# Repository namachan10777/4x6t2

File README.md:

# 4x6t2

[Imgur](https://i.imgur.com/xArgN0v.jpg)

A splited keyboard.
# License
MIT License 
Copyright (c) 2018 Nakano Masaki
## Exception
 * ./pcb/lib/4x6t2.pretty/MX_ALPS_KH_u1.00.kicad_mod
 * ./pcb/lib/4x6t2.pretty/D_SOD-123.kicad_mod
 * ./pcb/lib/4x6t2.pretty/LED_D3.0mm.kicad_mod
 * ./pcb/lib/4x6t2.pretty/R_Axial.kicad_mod
 * ./pcb/lib/4x6t2.pretty/SW_Tactile_SPST_Angled.kicad_mod
These footprint's original author is KiCAD.
These are distributed under CC-BY-SA 4.0.

# Third party
## helix
### point of use
 * Key footprint (./pcb/lib/4x6t2.pretty/MX_ALPS_KH_u1.00.kicad_mod) (modified)
 * Audio Jack footprint (./pcb/lib/4x6t2.pretty/MJ-4PP-9_rev2.kicad_mod)
### LICENSE
>Copyright (c) 2018 MakotoKurauchi
>
>Permission is hereby granted, free of charge, to any person obtaining a copy
>of this software and associated documentation files (the "Software"), to deal
>in the Software without restriction, including without limitation the rights
>to use, copy, modify, merge, publish, distribute, sublicense, and/or sell
>copies of the Software, and to permit persons to whom the Software is
>furnished to do so, subject to the following conditions:
>
>The above copyright notice and this permission notice shall be included in all
>copies or substantial portions of the Software.
>
>THE SOFTWARE IS PROVIDED "AS IS", WITHOUT WARRANTY OF ANY KIND, EXPRESS OR
>IMPLIED, INCLUDING BUT NOT LIMITED TO THE WARRANTIES OF MERCHANTABILITY,
>FITNESS FOR A PARTICULAR PURPOSE AND NONINFRINGEMENT. IN NO EVENT SHALL THE
>AUTHORS OR COPYRIGHT HOLDERS BE LIABLE FOR ANY CLAIM, DAMAGES OR OTHER
>LIABILITY, WHETHER IN AN ACTION OF CONTRACT, TORT OR OTHERWISE, ARISING FROM,
>OUT OF OR IN CONNECTION WITH THE SOFTWARE OR THE USE OR OTHER DEALINGS IN THE
>SOFTWARE.

## KiCAD Library
### LICENSE
CC-BY-SA 4.0
Copyright (c) KiCAD

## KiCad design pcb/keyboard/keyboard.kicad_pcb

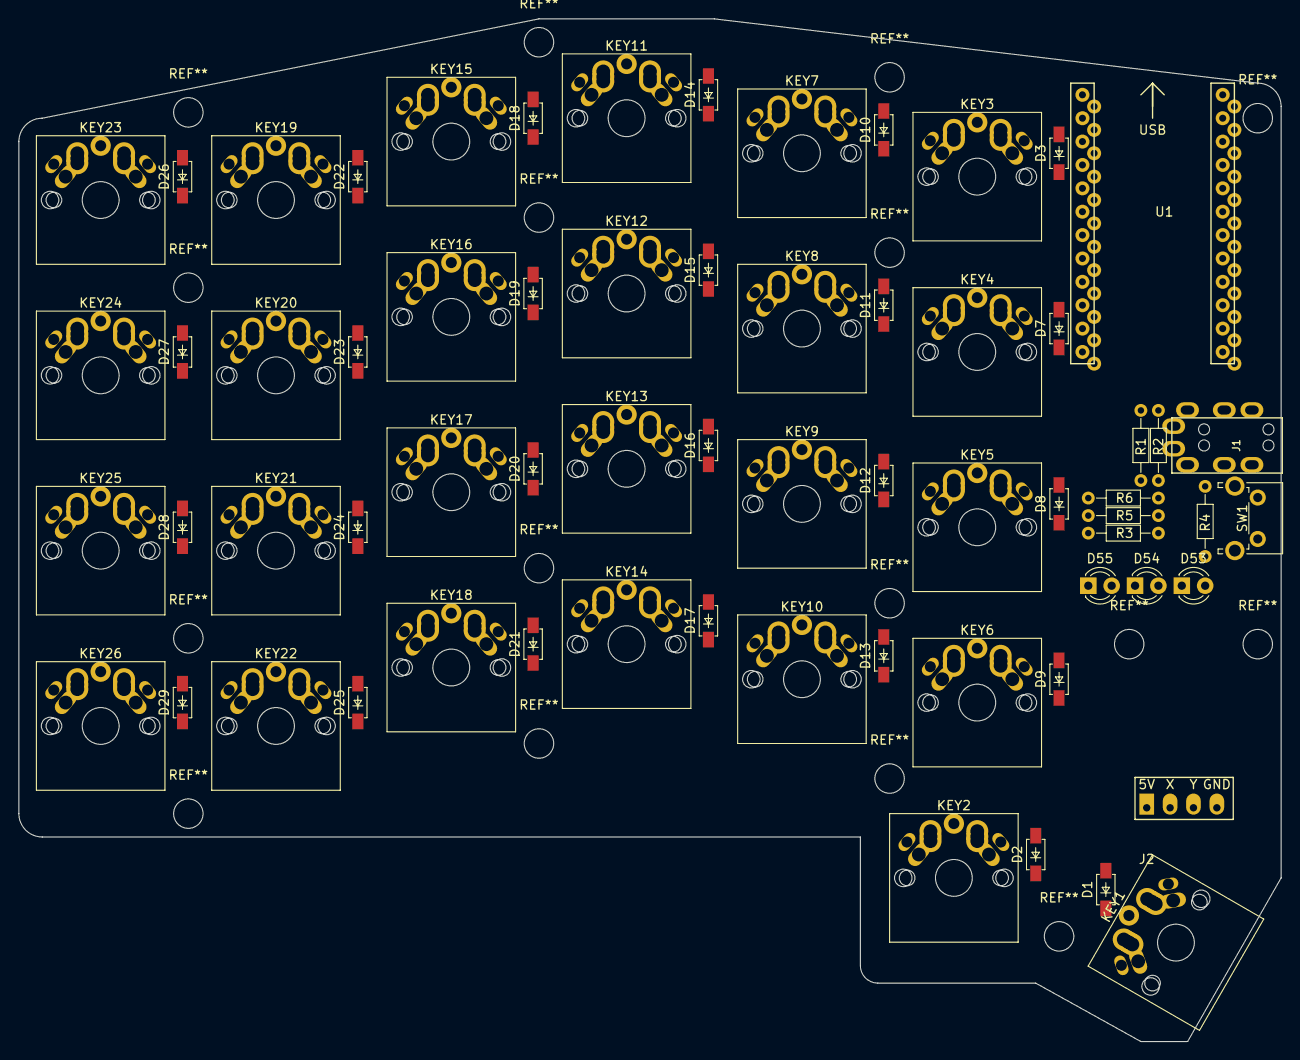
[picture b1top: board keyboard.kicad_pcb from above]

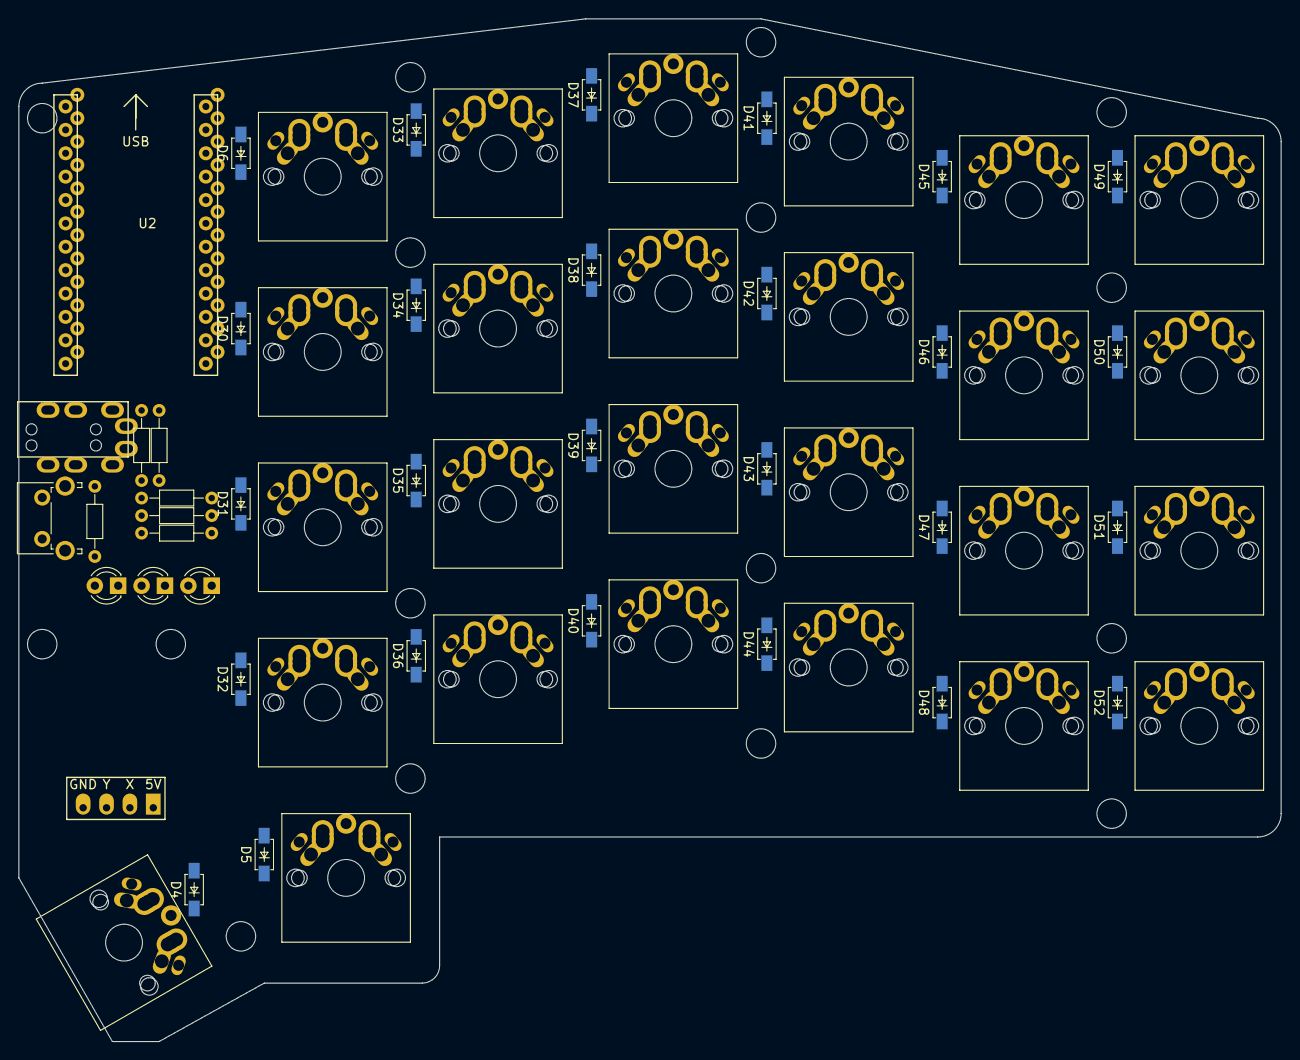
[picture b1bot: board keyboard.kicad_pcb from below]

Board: 2 copper layers, 137.2 x 111.1 mm, 92 parts (27 on the bottom side), 50 nets, no tracks yet.

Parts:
D1, D2, D3, D4, D5, D6, D7, D8, D9, D10, D11, D12, D13, D14, D15, D16, D17, D18, D19, D20, D21, D22, D23, D24, D25, D26, D27, D28, D29, D30, D31, D32, D33, D34, D35, D36, D37, D38, D39, D40, D41, D42, D43, D44, D45, D46, D47, D48, D49, D50, D51, D52: D; D_SOD-123
D53, D54, D55: LED; LED_D3.0mm
J1: Audio-Jack-4; MJ-4PP-9_rev2
J2: sidebutton; Wirepad_01x04
KEY1: KEY20; MX_ALPS_KH_u1.00
KEY2: KEY30; MX_ALPS_KH_u1.00
KEY3: KEY01; MX_ALPS_KH_u1.00
KEY4: KEY11; MX_ALPS_KH_u1.00
KEY5: KEY21; MX_ALPS_KH_u1.00
KEY6: KEY31; MX_ALPS_KH_u1.00
KEY7: KEY02; MX_ALPS_KH_u1.00
KEY8: KEY12; MX_ALPS_KH_u1.00
KEY9: KEY22; MX_ALPS_KH_u1.00
KEY10: KEY32; MX_ALPS_KH_u1.00
KEY11: KEY03; MX_ALPS_KH_u1.00
KEY12: KEY13; MX_ALPS_KH_u1.00
KEY13: KEY23; MX_ALPS_KH_u1.00
KEY14: KEY33; MX_ALPS_KH_u1.00
KEY15: KEY04; MX_ALPS_KH_u1.00
KEY16: KEY14; MX_ALPS_KH_u1.00
KEY17: KEY24; MX_ALPS_KH_u1.00
KEY18: KEY34; MX_ALPS_KH_u1.00
KEY19: KEY05; MX_ALPS_KH_u1.00
KEY20: KEY15; MX_ALPS_KH_u1.00
KEY21: KEY25; MX_ALPS_KH_u1.00
KEY22: KEY35; MX_ALPS_KH_u1.00
KEY23: KEY06; MX_ALPS_KH_u1.00
KEY24: KEY16; MX_ALPS_KH_u1.00
KEY25: KEY26; MX_ALPS_KH_u1.00
KEY26: KE36; MX_ALPS_KH_u1.00
R1, R2: 10kΩ; R_Axial
R3, R5, R6: 100Ω; R_Axial
R4: R; R_Axial
SW1: RESET_SW; SW_Tactile_SPST_Angled
U1, U2: Arduino_Pro_Micro

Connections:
+5V: J1.3, J2.1, R1.1, R2.1, R3.1, R4.1, R5.1, R6.1, U1.21, U2.21
/COL0: D1.2, D2.2, D4.2, D5.2, U1.17, U2.17
/COL1: D3.2, D6.2, D7.2, D8.2, D9.2, D30.2, D31.2, D32.2, U1.16, U2.16
/COL2: D10.2, D11.2, D12.2, D13.2, D33.2, D34.2, D35.2, D36.2, U1.15, U2.15
/COL3: D14.2, D15.2, D16.2, D17.2, D37.2, D38.2, D39.2, D40.2, U1.14, U2.14
/COL4: D18.2, D19.2, D20.2, D21.2, D41.2, D42.2, D43.2, D44.2, U1.13, U2.13
/COL5: D22.2, D23.2, D24.2, D25.2, D45.2, D46.2, D47.2, D48.2, U1.11, U2.11
/COL6: D26.2, D27.2, D28.2, D29.2, D49.2, D50.2, D51.2, D52.2, U1.12, U2.12
/LED1: D53.1, U1.20, U2.20
/LED2: D54.1, U1.19, U2.19
/LED3: D55.1, U1.18, U2.18
/ROW0: KEY3.1, KEY7.1, KEY11.1, KEY15.1, KEY19.1, KEY23.1, U1.1, U2.1
/ROW1: KEY4.1, KEY8.1, KEY12.1, KEY16.1, KEY20.1, KEY24.1, U1.2, U2.2
/ROW2: KEY1.1, KEY5.1, KEY9.1, KEY13.1, KEY17.1, KEY21.1, KEY25.1, U1.8, U2.8
/ROW4: KEY2.1, KEY6.1, KEY10.1, KEY14.1, KEY18.1, KEY22.1, KEY26.1, U1.10, U2.10
/RST: R4.2, SW1.1, U1.22, U2.22
/SCL: J1.1, R1.2, U1.6, U2.6
/SDA: J1.2, R2.2, U1.5, U2.5
/X: J2.2, U1.9, U2.9
/Y: J2.3, U1.7, U2.7
GND: J1.4, J2.4, SW1.2, U1.3, U1.4, U1.23, U2.3, U2.4, U2.23
unnamed: D1.1, D4.1, KEY1.2
unnamed: D2.1, D5.1, KEY2.2
unnamed: D3.1, D6.1, KEY3.2
unnamed: D10.1, D33.1, KEY7.2
unnamed: D11.1, D34.1, KEY8.2
unnamed: D12.1, D35.1, KEY9.2
unnamed: D13.1, D36.1, KEY10.2
unnamed: D14.1, D37.1, KEY11.2
unnamed: D15.1, D38.1, KEY12.2
unnamed: D16.1, D39.1, KEY13.2
unnamed: D17.1, D40.1, KEY14.2
unnamed: D18.1, D41.1, KEY15.2
unnamed: D19.1, D42.1, KEY16.2
unnamed: D20.1, D43.1, KEY17.2
unnamed: D21.1, D44.1, KEY18.2
unnamed: D22.1, D45.1, KEY19.2
unnamed: D23.1, D46.1, KEY20.2
unnamed: D24.1, D47.1, KEY21.2
unnamed: D25.1, D48.1, KEY22.2
unnamed: D26.1, D49.1, KEY23.2
unnamed: D27.1, D50.1, KEY24.2
unnamed: D28.1, D51.1, KEY25.2
unnamed: D29.1, D52.1, KEY26.2
unnamed: D7.1, D30.1, KEY4.2
unnamed: D8.1, D31.1, KEY5.2
unnamed: D9.1, D32.1, KEY6.2
unnamed: D53.2, R3.2
unnamed: D54.2, R5.2
unnamed: D55.2, R6.2

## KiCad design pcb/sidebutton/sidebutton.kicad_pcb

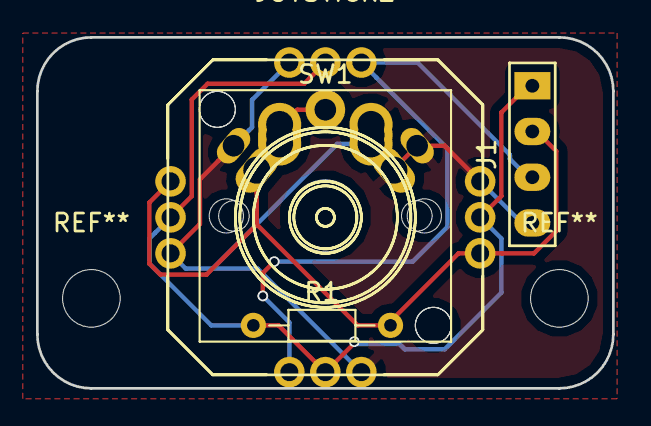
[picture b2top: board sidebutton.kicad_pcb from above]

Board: 2 copper layers, 32.0 x 19.5 mm, 5 parts (0 on the bottom side), 4 nets.

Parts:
J1: Conn_01x04; Wirepad_01x04
JOYSTICK1, JOYSTICK2: JT8P-3.2T-B10K-1-16Y
R1: R; R_Axial_DIN0204_L3.6mm_D1.6mm_P7.62mm_Horizontal
SW1: SW_DIP_x01; MX_ALPS_KH_u1.00

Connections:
+5V: J1.1, JOYSTICK1.2, JOYSTICK1.5, JOYSTICK2.2, JOYSTICK2.5, R1.1
/out1: J1.2, JOYSTICK1.4, JOYSTICK2.4, R1.2, SW1.2
/out2: J1.3, JOYSTICK1.1, JOYSTICK2.1
GND: J1.4, JOYSTICK1.3, JOYSTICK1.6, JOYSTICK2.3, JOYSTICK2.6, SW1.1

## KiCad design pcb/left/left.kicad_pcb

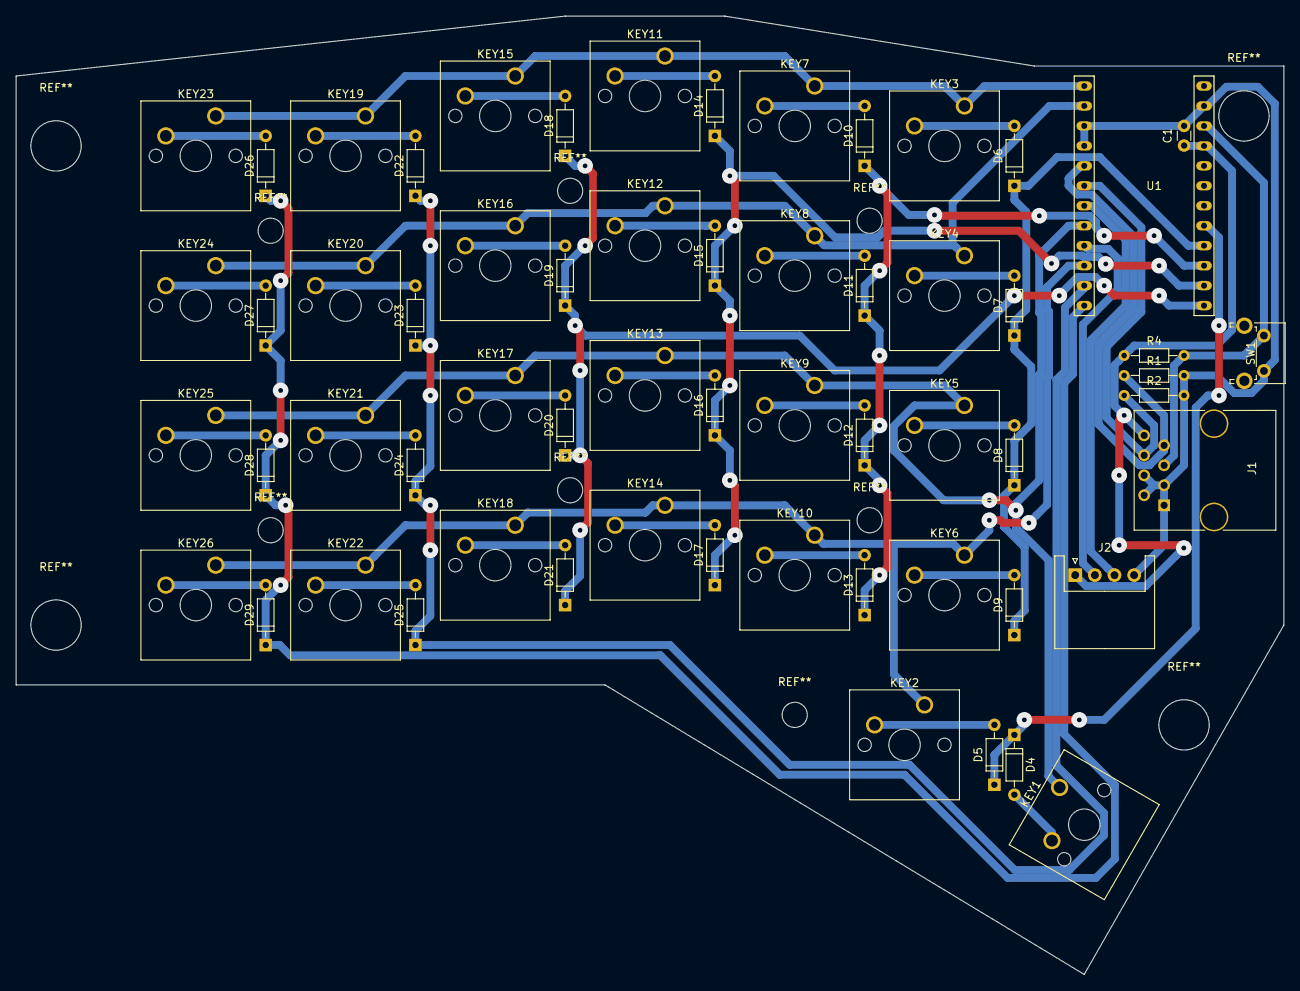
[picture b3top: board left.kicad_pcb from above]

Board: 2 copper layers, 161.3 x 121.9 mm, 60 parts (0 on the bottom side), 44 nets.

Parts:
C1: C; C_Disc_D3.0mm_W1.6mm_P2.50mm
D4, D5, D6, D7, D8, D9, D10, D11, D12, D13, D14, D15, D16, D17, D18, D19, D20, D21, D22, D23, D24, D25, D26, D27, D28, D29: D; D_DO-35_SOD27_P7.62mm_Horizontal
J1: RJ45-8pin; RJ45_8
J2: sidebutton; JST_XH_S04B-XH-A_04x2.50mm_Angled
KEY1: KEY20; SW_Cherry_MX1A_1.00u_PCB
KEY2: KEY30; SW_Cherry_MX1A_1.00u_PCB
KEY3: KEY01; SW_Cherry_MX1A_1.00u_PCB
KEY4: KEY11; SW_Cherry_MX1A_1.00u_PCB
KEY5: KEY21; SW_Cherry_MX1A_1.00u_PCB
KEY6: KEY31; SW_Cherry_MX1A_1.00u_PCB
KEY7: KEY02; SW_Cherry_MX1A_1.00u_PCB
KEY8: KEY12; SW_Cherry_MX1A_1.00u_PCB
KEY9: KEY22; SW_Cherry_MX1A_1.00u_PCB
KEY10: KEY32; SW_Cherry_MX1A_1.00u_PCB
KEY11: KEY03; SW_Cherry_MX1A_1.00u_PCB
KEY12: KEY13; SW_Cherry_MX1A_1.00u_PCB
KEY13: KEY23; SW_Cherry_MX1A_1.00u_PCB
KEY14: KEY33; SW_Cherry_MX1A_1.00u_PCB
KEY15: KEY04; SW_Cherry_MX1A_1.00u_PCB
KEY16: KEY14; SW_Cherry_MX1A_1.00u_PCB
KEY17: KEY24; SW_Cherry_MX1A_1.00u_PCB
KEY18: KEY34; SW_Cherry_MX1A_1.00u_PCB
KEY19: KEY05; SW_Cherry_MX1A_1.00u_PCB
KEY20: KEY15; SW_Cherry_MX1A_1.00u_PCB
KEY21: KEY25; SW_Cherry_MX1A_1.00u_PCB
KEY22: KEY35; SW_Cherry_MX1A_1.00u_PCB
KEY23: KEY06; SW_Cherry_MX1A_1.00u_PCB
KEY24: KEY16; SW_Cherry_MX1A_1.00u_PCB
KEY25: KEY26; SW_Cherry_MX1A_1.00u_PCB
KEY26: KE36; SW_Cherry_MX1A_1.00u_PCB
R1, R2: 10kΩ; R_Axial_DIN0204_L3.6mm_D1.6mm_P7.62mm_Horizontal
R4: R; R_Axial_DIN0204_L3.6mm_D1.6mm_P7.62mm_Horizontal
SW1: RESET_SW; SW_Tactile_SPST_Angled_PTS645Vx31-2LFS
U1: Arduino_Pro_Micro

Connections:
+5V: C1.1, J1.8, J2.1, R4.1, U1.21
/COL0: D4.1, D5.1, U1.17
/COL1: D6.1, D7.1, D8.1, D9.1, U1.16
/COL2: D10.1, D11.1, D12.1, D13.1, U1.15
/COL3: D14.1, D15.1, D16.1, D17.1, U1.14
/COL4: D18.1, D19.1, D20.1, D21.1, U1.13
/COL5: D22.1, D23.1, D24.1, D25.1, U1.11
/COL6: D26.1, D27.1, D28.1, D29.1, U1.12
/ROW0: KEY3.1, KEY7.1, KEY11.1, KEY15.1, KEY19.1, KEY23.1, U1.1
/ROW1: KEY4.1, KEY8.1, KEY12.1, KEY16.1, KEY20.1, KEY24.1, U1.2
/ROW2: KEY1.1, KEY5.1, KEY9.1, KEY13.1, KEY17.1, KEY21.1, KEY25.1, U1.8
/ROW4: KEY2.1, KEY6.1, KEY10.1, KEY14.1, KEY18.1, KEY22.1, KEY26.1, U1.10
/RST: J1.5, R4.2, SW1.1, U1.22
/SCL: J1.6, R2.1, U1.6
/SDA: J1.7, R1.1, U1.5
/X: J2.2, U1.9
/Y: J2.3, U1.7
GND: C1.2, J1.1, J1.2, J1.3, J1.4, J2.4, R1.2, R2.2, SW1.2, U1.3, U1.4, U1.23
unnamed: D4.2, KEY1.2
unnamed: D5.2, KEY2.2
unnamed: D6.2, KEY3.2
unnamed: D7.2, KEY4.2
unnamed: D8.2, KEY5.2
unnamed: D9.2, KEY6.2
unnamed: D10.2, KEY7.2
unnamed: D11.2, KEY8.2
unnamed: D12.2, KEY9.2
unnamed: D13.2, KEY10.2
unnamed: D14.2, KEY11.2
unnamed: D15.2, KEY12.2
unnamed: D16.2, KEY13.2
unnamed: D17.2, KEY14.2
unnamed: D18.2, KEY15.2
unnamed: D19.2, KEY16.2
unnamed: D20.2, KEY17.2
unnamed: D21.2, KEY18.2
unnamed: D22.2, KEY19.2
unnamed: D23.2, KEY20.2
unnamed: D24.2, KEY21.2
unnamed: D25.2, KEY22.2
unnamed: D26.2, KEY23.2
unnamed: D27.2, KEY24.2
unnamed: D28.2, KEY25.2
unnamed: D29.2, KEY26.2

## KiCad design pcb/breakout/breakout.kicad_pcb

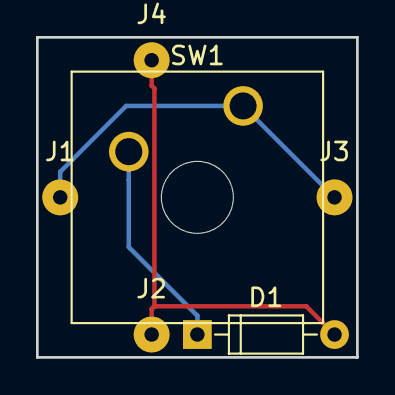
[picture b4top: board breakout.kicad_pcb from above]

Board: 2 copper layers, 17.8 x 17.8 mm, 6 parts (0 on the bottom side), 3 nets.

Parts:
D1: D; D_DO-35_SOD27_P7.62mm_Horizontal
J1, J2, J3, J4: Conn_01x01; SolderWirePad_single_0-8mmDrill
SW1: SW_DIP_x01; SW_Cherry_MX1A_1.00u_Plate

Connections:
unnamed: D1.1, SW1.2
unnamed: D1.2, J2.1, J4.1
unnamed: J1.1, J3.1, SW1.1

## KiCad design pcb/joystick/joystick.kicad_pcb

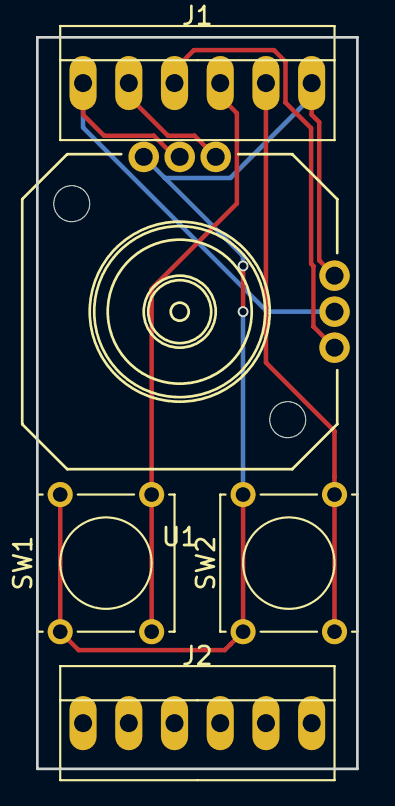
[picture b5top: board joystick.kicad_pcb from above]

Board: 2 copper layers, 17.8 x 40.6 mm, 5 parts (0 on the bottom side), 6 nets.

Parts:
J1, J2: Conn_01x06; PINHEAD1-6
SW1, SW2: SW_DIP_x01; SW_Tactile_Straight_KSL0Axx1LFTR
U1: JT8P-3.2T-B10K-1-16Y

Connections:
+5V: J1.1, U1.2, U1.5
/sw1: J1.4, SW1.2
/sw2: J1.5, SW2.2
/x: J1.3, U1.4
/y: J1.2, U1.1
GND: J1.6, SW1.1, SW2.1, U1.3, U1.6

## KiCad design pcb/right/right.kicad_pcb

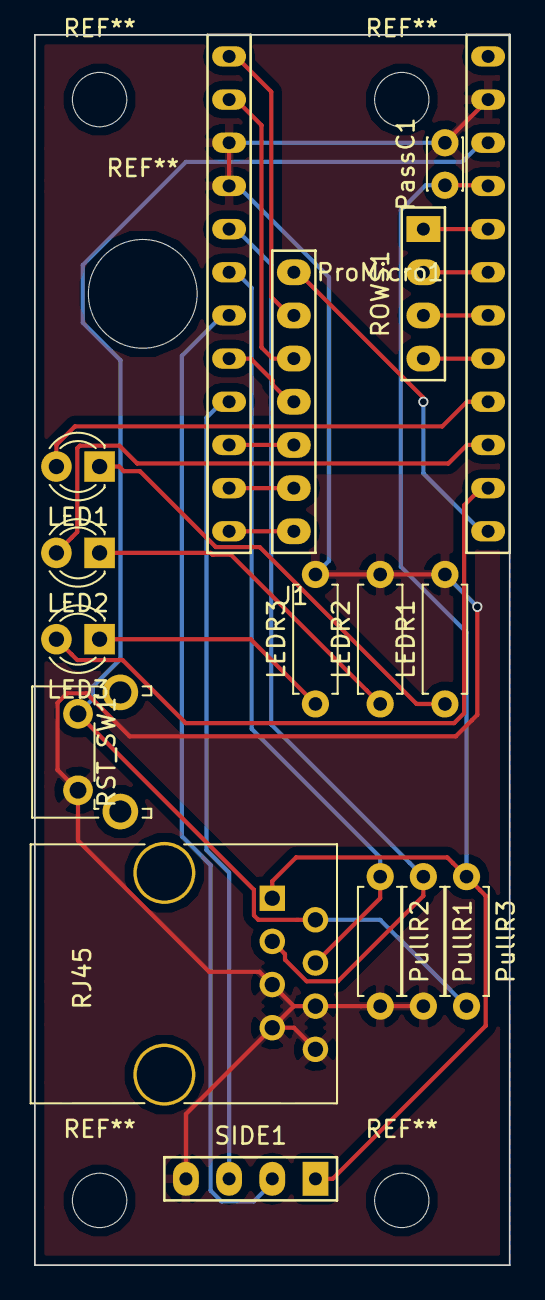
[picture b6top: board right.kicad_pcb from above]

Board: 2 copper layers, 27.9 x 72.4 mm, 16 parts (0 on the bottom side), 24 nets.

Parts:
J1: Conn_01x07; Wirepad_01x07
LED1: LED1; LED_D3.0mm
LED2: LED2; LED_D3.0mm
LED3: LED3; LED_D3.0mm
LEDR1: LED1_R; R_Axial_DIN0207_L6.3mm_D2.5mm_P7.62mm_Horizontal
LEDR2: LED2_R; R_Axial_DIN0207_L6.3mm_D2.5mm_P7.62mm_Horizontal
LEDR3: LED3_R; R_Axial_DIN0207_L6.3mm_D2.5mm_P7.62mm_Horizontal
PassC1: PassC; C_Disc_D3.0mm_W2.0mm_P2.50mm
ProMicro1: Arduino_Pro_Micro
PullR1, PullR2: I2C_PR; R_Axial_DIN0207_L6.3mm_D2.5mm_P7.62mm_Horizontal
PullR3: RST_PR; R_Axial_DIN0207_L6.3mm_D2.5mm_P7.62mm_Horizontal
RJ45: RJ45-8pin; RJ45_8
ROWS1: Conn_01x04; Wirepad_01x04
RST_SW1: RST_Switch; SW_Tactile_SPST_Angled_PTS645Vx31-2LFS
SIDE1: Conn_01x04; Wirepad_01x04

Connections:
+5V: PassC1.1, ProMicro1.21, PullR3.1, RJ45.1, SIDE1.1
/COL0: J1.2, ProMicro1.1
/COL1: J1.3, ProMicro1.2
/COL2: J1.4, ProMicro1.8
/COL3: J1.5, ProMicro1.10
/COL4: J1.6, ProMicro1.11
/COL5: J1.7, ProMicro1.12
/LED1: LED1.2, ProMicro1.16
/LED2: LED2.2, ProMicro1.15
/LED3: LED3.2, ProMicro1.14
/ROW0: ProMicro1.20, ROWS1.1
/ROW1: ProMicro1.19, ROWS1.2
/ROW2: ProMicro1.18, ROWS1.3
/ROW3: ProMicro1.17, ROWS1.4
/RST: ProMicro1.22, PullR3.2, RJ45.2, RST_SW1.2
/SCL: ProMicro1.6, PullR2.1, RJ45.4
/SDA: ProMicro1.5, PullR1.1, RJ45.3
/Thumb_key: J1.1, ProMicro1.13
/X: ProMicro1.7, SIDE1.2
/Y: ProMicro1.9, SIDE1.3
GND: LEDR1.2, LEDR2.2, LEDR3.2, PassC1.2, ProMicro1.3, ProMicro1.4, ProMicro1.23, PullR1.2, PullR2.2, RJ45.5, RJ45.6, RJ45.7, RJ45.8, RST_SW1.1, SIDE1.4
unnamed: LED1.1, LEDR1.1
unnamed: LED2.1, LEDR2.1
unnamed: LED3.1, LEDR3.1

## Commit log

2018-02-18 add README.md
2018-02-18 add RJ45-8pin KiCADのRJ45はフットプリントと対応してない(なんで)ので
2018-02-18 lib: add Arduino Pro Micro
2018-02-19 left: add schematic
2018-02-19 add 30 degree rotated key footprint
2018-02-19 add joystick to lib
2018-02-19 add joystic to schematic
2018-02-19 add left pcb arrangement
2018-02-20 add joystick pcb
2018-02-20 ignore *-cache.lib
2018-02-20 improve pcb design
2018-02-21 improve key arrangement
2018-02-22 add plate artwork
2018-02-23 fix sidebutton めっちゃブリッジしそうで怖い
2018-02-23 small pcb キーの配線は空中配線で
2018-02-23 left: place all parts
2018-02-23 improve basic design
2018-02-24 sidebutton pcb became reversible
2018-02-24 fix sidebutton pcb 穴間の修正
2018-02-24 add spacer source code
2018-02-24 resize pcb shorten pcb length a bit.
2018-02-24 avoid vmount and pcb conflict
2018-02-24 wiring left
2018-02-24 fix LED arrangement LED conflicted with Pro Micro
2018-02-24 add right pcb
2018-02-24 add license badge
2018-02-24 remove unused script
2018-02-25 fix pcb size
2018-02-25 fix hole position of vmount.scad
2018-02-25 add large_spacer.scad
2018-02-25 fix hole position
2018-02-25 add STL file
2018-02-25 add pcb cover
2018-02-25 add joystick cover
2018-02-25 rename spacer -> 3dparts
2018-02-26 ignore gerber data
2018-02-26 add packing script
2018-02-26 add elecrow support
2018-02-27 improve parts arrangement
2018-02-27 improve pcb size
2018-02-27 fix plate
2018-02-27 connect pad
2018-02-27 fix packing script bug
2018-02-27 add Cherry MX breakout
2018-02-27 reduction breakout
2018-02-27 add panelized breakout
2018-02-27 add parts list
2018-03-01 ignore dril file
2018-03-04 left: large pcb
2018-03-04 add hybrid keyboard footprint
2018-03-05 fix pcb outline
2018-03-05 add reversible keyboard pcb
2018-03-05 fix packing script
2018-03-05 improve packing script output msg
2018-03-05 minimize vmout
2018-03-05 fix plate design
2018-03-05 fix sidebutton pcb design
2018-03-05 connect 2 vmount
2018-03-07 add Kailh low profile adapted footprint
2018-03-07 place new key footprints
2018-03-07 tweak little finger key position
2018-03-07 add third party license
2018-03-07 add reversible 4p audio jack
2018-03-07 audio jack footprint: fix pin number
2018-03-07 RJ45 -> Audio Jack 4pin
2018-03-07 wiring
2018-03-07 sidebutton use KH key
2018-03-07 imporve design
    * 小指の担当部の薬指との差をゆるく
    * PCBの切り詰め(強度はプレートで担保)
2018-03-07 fix vmount.scad
2018-03-07 abolish trancated 値段変わらなくない?
2018-03-09 fix top plate cut for pro micro and audio jack
2018-03-10 keyboard pcb: add R
2018-03-10 sidebutton pcb: add R
2018-03-10 packing script: fix missing drill data bug
2018-03-10 packing script: vender setting from command line
2018-03-10 add release file generate script
2018-03-10 release script: fix elecrow drill data is gerber. But fusionpcb request postscript drill data.
2018-03-11 release script: fix
2018-03-11 change pro micro footprint
2018-03-11 fix pro micro upside donw
2018-03-11 sidebutton conn: XH -> Wirepad
2018-03-11 fix vmount.scad height horizontal screw: M3 -> M2.5
2018-03-11 fix spacers
2018-03-11 sidebutton: add GND solid
2018-03-12 switching diode: THT -> SMD
2018-03-12 remove bottom plate lightening holes
2018-03-12 missing commit
2018-03-12 add gitattribute
2018-03-12 change space between top plate and under plate
    4.6 -> 4.2 mm
2018-03-12 confirm plate thickness
2018-03-12 fix sidebutton mounting position
2018-03-14 fix legal info
2018-03-14 adapt allpcb
2018-03-14 i2c: pull down -> pull up
2018-03-14 add missing R
2018-03-14 fix spacer height
2018-03-15 add LED
2018-03-16 emlarge via drill size 0.2032 -> 0.3
2018-03-16 add cleaning script
2018-03-22 improve footprints
2018-03-24 improve promicro footprint
2018-03-24 improve silk and holes
2018-04-17 fix schematic
2018-05-07 add img
2018-05-07 fix img url
